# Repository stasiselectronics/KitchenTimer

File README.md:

# KitchenTimer

Welcome to the source files!

Here you can find all the files and folders needed to replicate or redesign this project!

This circuit board is designed to bring together a WiFi enabled microcontroller with a 4 character segmented LED display. 

# Current Status

I have recieved the first round of boards and began prototyping the electronics assembly.

The firmwware has some more work needed before it can display numbers and adjust brightness.

The board has a few things that need to be fixed before the next round of PCB fabrication.

I should try and get a PCB order soon, before the end of the year.

# Documentation

Not a lot of documentation except for the source files. If you have a question regarding this design, don't hesitate to open an issue on this repository

# Licenses

The design files for this project are covered under 

CERN-OHL-S

Cern Open Hardware License - Strongly Reciprocal

[View Full License Text](https://ohwr.org/cern_ohl_s_v2.pdf)

## Folder Structure

The project is separated into main categories at the root of the project folder. I use "Hardware Files" to hold all of the printed circuit board design files. I also use some other descriptive names and keep them consistent amongst projects:

- **Enclosure Files** : 3D printed or somehow otherwise fabricated. All the files needed for the box the project might end up in.
- **Firmware Files** : The code for any microcontrollers that might end up on the boards. 
- **Mechanical Files** : Any CAD files for fabricating parts for the project. 

## Libraries

The KiCAD project has a project specific library that can be used for keeping the custom designed footprints and symbols.

By default it isn't a global library, so if you would like to use the footprints or symbols in another project be sure to change it to a "global" library.

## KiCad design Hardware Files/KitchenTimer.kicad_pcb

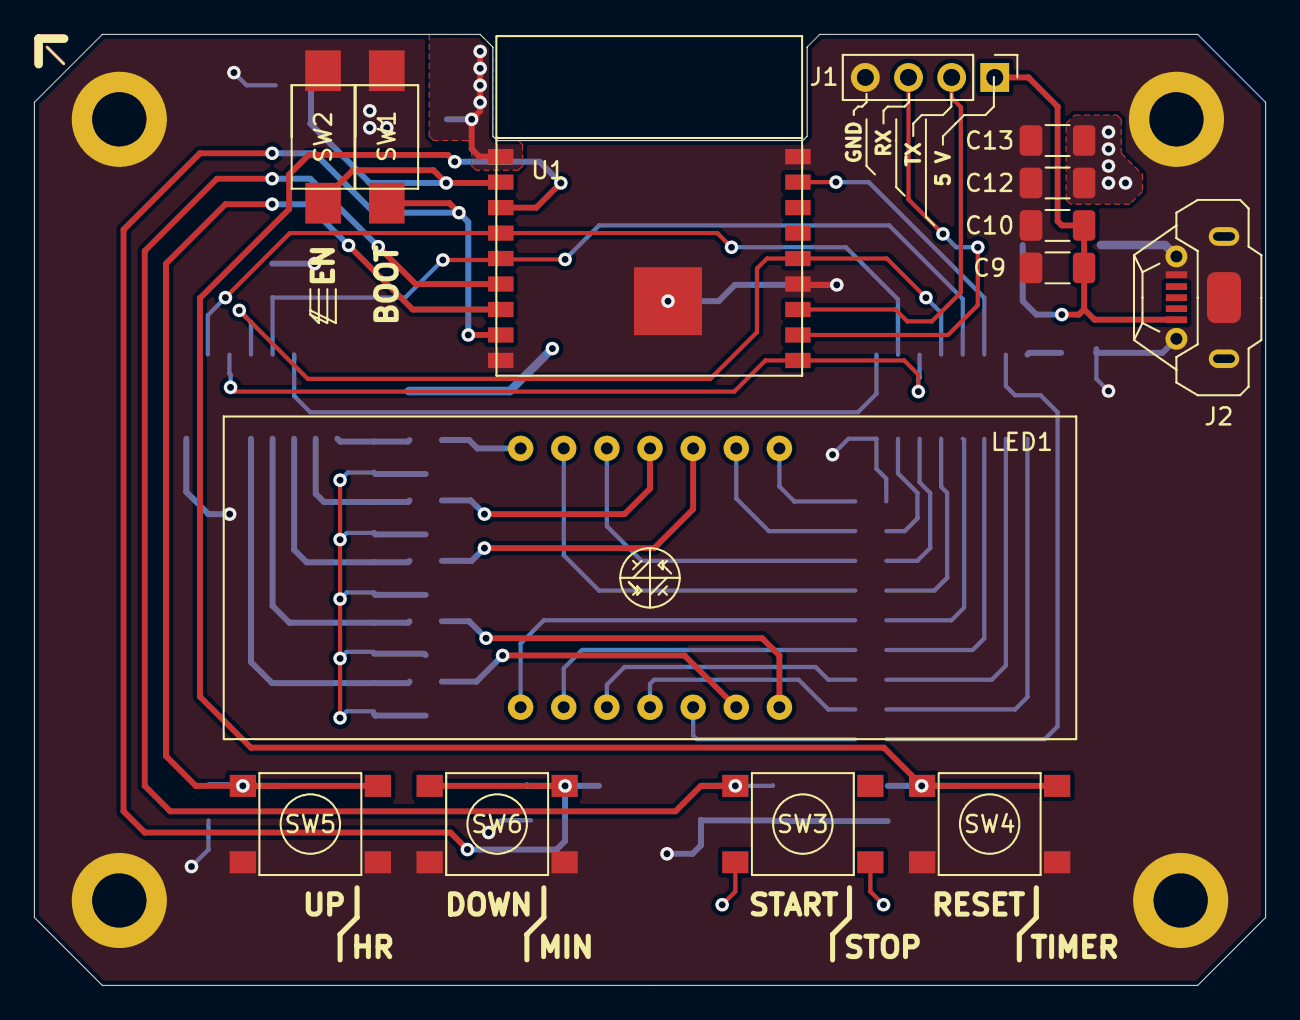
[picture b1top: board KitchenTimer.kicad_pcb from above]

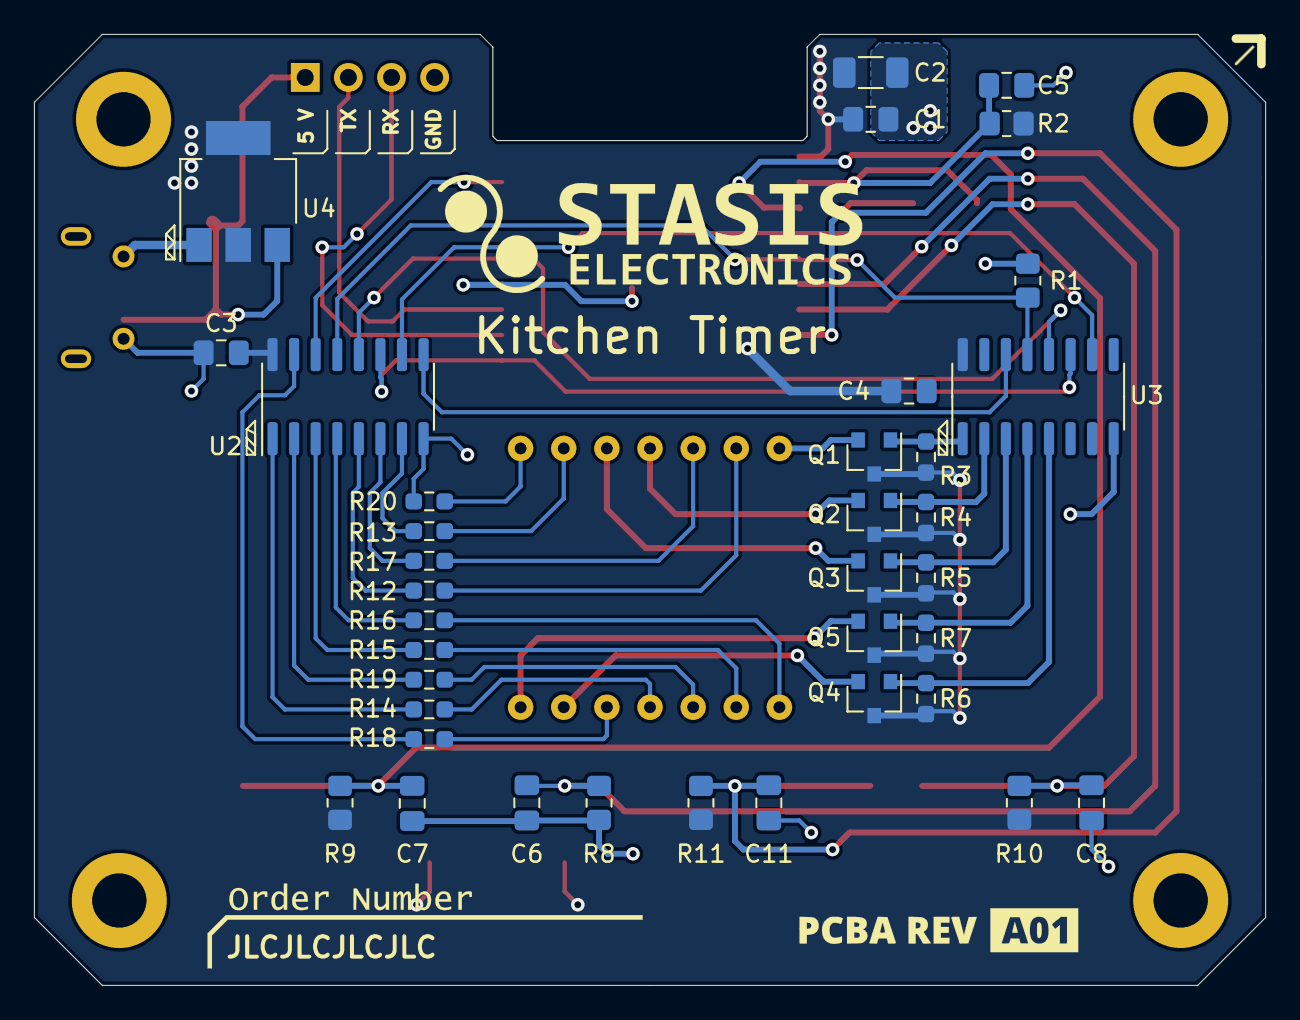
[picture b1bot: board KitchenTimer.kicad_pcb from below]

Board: 2 copper layers, 72.5 x 56.0 mm, 55 parts (37 on the bottom side), 43 nets.

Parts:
C1, C3, C4, C5, C6, C7, C8, C11: 1uF; C_0805_2012Metric_Pad1.18x1.45mm_HandSolder
C2, C9, C13: 10uF; C_1206_3216Metric_Pad1.33x1.80mm_HandSolder
C10, C12: 220nF; C_1206_3216Metric_Pad1.33x1.80mm_HandSolder
J1: 2.54mm 1x4; PinHeader_1x04_P2.54mm_Vertical
J2: MicroUSB; U-F-M5DD-Y-L
J3, J4, J5, J6: Mounting Hole; MountingHole_3.2mm_M3_DIN965_Pad
LED1: Blue 4 Char LED 0.56" (CA); SLR0564DBA4BD
Q1, Q2, Q3, Q4, Q5: PFET 1V 250uA 4A SOT-23; SOT-23
R1, R2, R8, R9, R10, R11: 10k; R_0805_2012Metric_Pad1.20x1.40mm_HandSolder
R3, R4, R5, R6, R7: 10k; R_0603_1608Metric_Pad0.98x0.95mm_HandSolder
R12, R13, R14, R15, R16, R17, R18, R19, R20: 10Ω; R_0603_1608Metric_Pad0.98x0.95mm_HandSolder
SW1, SW2: SPST; PTS636_SM25F_SMTR_LFS
SW3, SW4, SW5, SW6: SPST; PTS645SK50SMTR92LFS
U1: ESP-WROOM-02D
U2, U3: Serial to Parallel Shift Register; SOIC-16_3.9x9.9mm_P1.27mm
U4: 3.3 V Linear Regulator; SOT-223-3_TabPin2

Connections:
!Clear: U1.4, U2.10, U3.10
+3V3: C1.2, C2.1, C3.1, C4.1, C12.1, C13.1, Q1.3, Q2.3, Q3.3, Q4.3, Q5.3, R2.1, R3.2, R4.2, R5.2, R6.2, R7.2, R9.1, R10.1, R11.1, SW3.2, SW3.4, U1.1, U2.16, U3.16, U4.2
+5V: C9.1, C10.1, J1.1, J2.1, U4.3
BTN_Down: C11.1, R11.2, SW1.1, SW6.1, SW6.3, U1.8
BTN_ResetCountdown: C7.1, R9.2, SW4.1, SW4.3, U1.3
BTN_StartStop: C6.1, R8.1, SW3.1, SW3.3, U1.6
BTN_Up: C8.1, R10.2, SW5.1, SW5.3, U1.7
Char_1: Q1.1, R3.1, U3.1
Char_1_Power: LED1.14, Q1.2
Char_2: Q2.1, R4.1, U3.2
Char_2_Power: LED1.11, Q2.2
Char_3: Q3.1, R5.1, U3.3
Char_3_Power: LED1.10, Q3.2
Char_4: Q4.1, R6.1, U3.5
Char_4_Power: LED1.6, Q4.2
Char_(':')_Power: LED1.7, Q5.2
Clock: U1.10, U2.11, U3.11
Data: U1.17, U2.14
ESP_Enable: C5.1, R2.2, SW2.1, U1.2
ESP_RX: J1.3, U1.11
ESP_TX: J1.2, U1.12
GND: C1.1, C2.2, C3.2, C4.2, C5.2, C6.2, C7.2, C8.2, C9.2, C10.2, C11.2, C12.2, C13.2, J1.4, J2.5, J2.6, J3.1, J4.1, J5.1, J6.1, R1.1, R8.2, R20.2, SW1.2, SW2.2, SW4.2, SW4.4, SW5.2, SW5.4, SW6.2, SW6.4, U1.9, U1.13, U1.18, U1.19, U2.8, U3.8, U4.1
LED_(':'): Q5.1, R7.1, U3.4
LED_A: R12.2, U2.5
LED_B: R13.2, U2.7
LED_C: R14.2, U2.1
LED_D: R15.2, U2.3
LED_DP: R19.2, U2.2
LED_E: R16.2, U2.4
LED_F: R17.2, U2.6
LED_G: R18.2, U2.15
Latch: U1.14, U2.12, U3.12
unnamed: LED1.1, R16.1
unnamed: LED1.2, R15.1
unnamed: LED1.3, R19.1
unnamed: LED1.4, R14.1
unnamed: LED1.5, R18.1
unnamed: LED1.8, R20.1
unnamed: LED1.9, R13.1
unnamed: LED1.12, R17.1
unnamed: LED1.13, R12.1
ShiftRegister_1_overflow: U2.9, U3.14
ShiftRegister_Output_Enable: R1.2, U1.5, U2.13, U3.13

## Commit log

2021-09-26 Change project name to KitchenTimer
2021-09-26 update library
2021-09-26 add 7 segment led symbol
2021-09-26 add led display and driver circuit
2021-09-26 add esp8266
2021-09-26 add boost converter circuits
2021-09-26 update boost converter circuit
2021-09-26 add sub sheets
2021-09-26 move circuits into subsheets
2021-09-27 Adjust sheet properties and output schematics
2021-09-27 add voltage regulators
2021-09-27 add up and down buttons
2021-09-27 add voltage source selection for LEDs
2021-09-27 remove extra pull down resistor
2021-09-27 remove mosfet for ":" char current sink
2021-09-27 add led display footprint
2021-09-27 add 3d body
2021-09-27 update footprint for symbol
2021-09-27 push components to PCB
2021-09-27 remove current limit resistors to each char
2021-09-27 change resistors to 0805
2021-09-27 fix ground naming
2021-09-27 update layout
2021-09-27 reorganize mosfets
2021-09-27 layout mosfets
2021-09-28 change architecture approach
2021-09-29 update shift register
2021-10-01 reduce complexity and improve layout
2021-10-01 trying out submodules
2021-10-01 remove old files
2021-10-01 update library references
2021-10-01 add gnd connection
2021-10-01 add 3d model link
2021-10-01 update footprint step file references
2021-10-02 Fix designator issues
2021-10-02 reposition designators
2021-10-03 fix shift register pin mapping and routing
2021-10-03 update schematic layout
2021-10-03 add SVGs
2021-10-03 update components
2021-10-03 finalize layout
2021-10-03 update library path
2021-10-03 finalize silkscreen layers
2021-10-03 add gerber files
2021-10-03 add gerber zip
2021-10-03 finalize output files
2021-10-03 update pdf
2021-10-03 add BOM
2021-10-03 Finalize Items
2021-10-06 update 1µF Capacitors
2021-10-18 remove OC field
2021-10-18 update part info
2021-10-18 update bill of materials
2021-10-21 Fix zone priority causing short to ground
2021-10-21 Add starter sketch for firmware testing
2021-10-21 switch IO to active high with pulldown to enable UART download
2021-10-21 fix which net is changed
2021-10-21 update pcb layout to fix IO15 needing pull down
